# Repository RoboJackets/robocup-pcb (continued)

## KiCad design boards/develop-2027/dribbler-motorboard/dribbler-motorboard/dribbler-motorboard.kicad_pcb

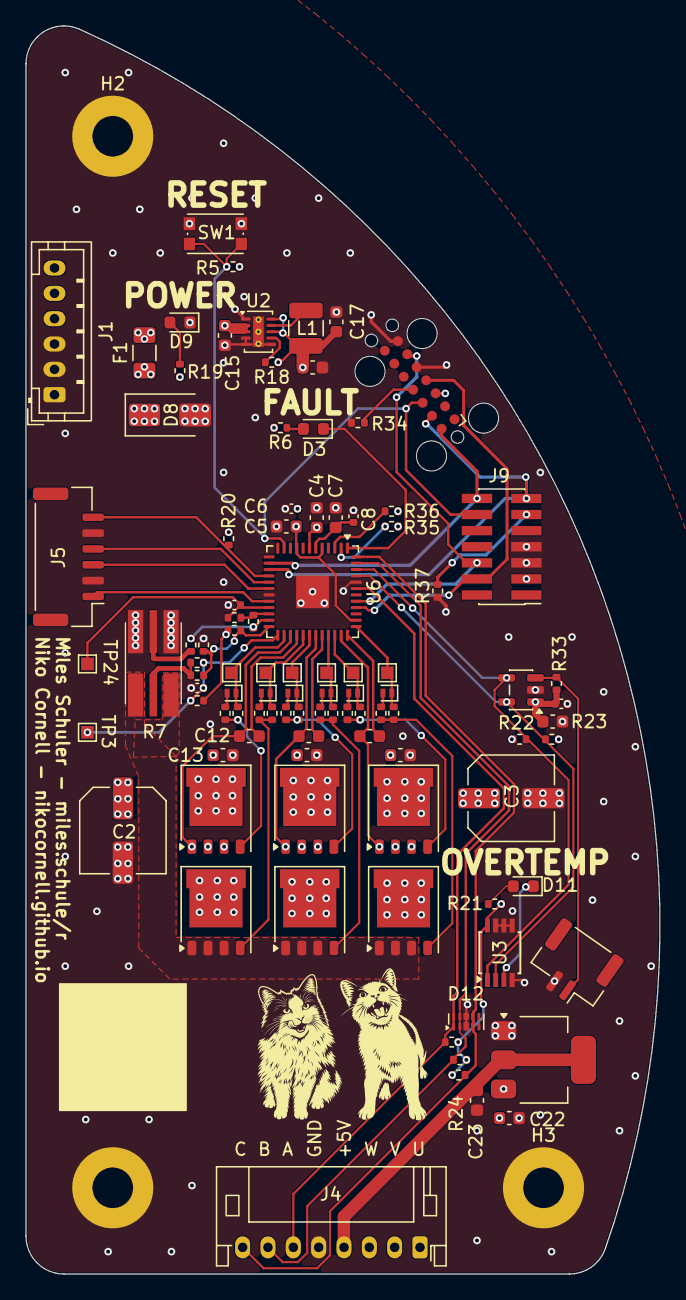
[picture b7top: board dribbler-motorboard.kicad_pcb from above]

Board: 4 copper layers, 50.0 x 98.5 mm, 101 parts (0 on the bottom side), 64 nets.

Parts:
C1, C4, C5, C9, C11, C12, C13, C14, C15, C23: 1u 63V; C_0603_1608Metric
C2, C3: 100u 35V; C_Elec_6.3x5.8
C6, C8, C20: 100n 25V; C_0402_1005Metric
C7, C16, C17, C19: 10u 25V; C_0603_1608Metric
C10: 33nF; C_0402_1005Metric
C18: 1n 25V; C_0402_1005Metric
C22: 4.7uF; C_0603_1608Metric
D1, D2, D4, D5, D6, D7: 1N4148WL2-TP; D_SOD-882
D3: FAULT; LED_0603_1608Metric
D8: SMAJ16A; D_SMA
D9: +12V; LED_0603_1608Metric
D11: OVERTEMP; LED_0603_1608Metric
D12: PUSB3FR4Z; Diodes_UDFN-10_1x2.5mm_P0.5mm
F1: 12A; Fuse_1206_3216Metric
H2, H3, H4: Corner; MountingHole_3.2mm_M3_Pad
J1: PWR_IN; JST_PH_B6B-PH-K_1x06_P2.00mm_Vertical
J4: MOTOR PHASE; JST_PH_S8B-PH-K_1x08_P2.00mm_Horizontal
J5: COMM SPI; JST_GH_BM06B-GHS-TBT_1x06-1MP_P1.25mm_Vertical
J7: Conn_01x02; JST_GH_SM02B-GHS-TB_1x02-1MP_P1.25mm_Horizontal
J8: Conn_ST_STDC14; Tag-Connect_TC2070-IDC-FP_2x07_P1.27mm_Vertical
J9: Conn_ST_STDC14; PinHeader_2x07_P1.27mm_Vertical_SMD
L1: 10u 540mA; L_1210_3225Metric
Q1, Q2, Q3, Q4, Q5, Q6: STL90N10F7; PQFN-8-EP_6x5mm_P1.27mm_Generic
R1, R3, R10, R12, R14, R16: 0R; R_0402_1005Metric
R2, R4, R11, R13, R15, R17: 68R; R_0402_1005Metric
R5, R19, R20, R24, R25, R26, R33, R35, R36: 10k; R_0402_1005Metric
R6, R21, R22, R23: 4.7k; R_0402_1005Metric
R7: 15m ±1% 3W; R_Shunt_Analog_2512_6332_HighAccuracy
R8: 1.13k ±0.1%; R_0402_1005Metric
R9: 33 ±0.1%; R_0402_1005Metric
R18: 100k; R_0402_1005Metric
R27: 120k ±0.1%; R_0402_1005Metric
R28, R31: 30k ±0.1%; R_0402_1005Metric
R29, R32: 240k ±0.1%; R_0402_1005Metric
R30: 300R ±1%; R_0402_1005Metric
R34, R37: 100; R_0402_1005Metric
SW1: RESET; SW_Push_1P1T_NO_CK_KMR2
TP3: OCCOMP; TestPoint_Pad_1.0x1.0mm
TP4: HSU; TestPoint_Pad_1.0x1.0mm
TP5: LSU; TestPoint_Pad_1.0x1.0mm
TP6: HSV; TestPoint_Pad_1.0x1.0mm
TP7: LSV; TestPoint_Pad_1.0x1.0mm
TP8: HSW; TestPoint_Pad_1.0x1.0mm
TP9: LSW; TestPoint_Pad_1.0x1.0mm
TP24: ISENSEx; TestPoint_Pad_1.0x1.0mm
U1: MCP3021; SOT-23-5
U2: TPS62177DQC; WSON-10-1EP_2x3mm_P0.5mm_EP0.84x2.4mm_ThermalVias
U3: LM75ADP; TSSOP-8_3x3mm_P0.65mm
U5: LDL1117S50R; SOT-223
U6: STSPIN32G0B2; VQFN-48-1EP_7x7mm_P0.5mm_EP2.6x2.6mm

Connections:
+3.3V: C5.1, C6.1, C16.1, C17.1, C19.1, C20.1, J8.3 (VCC), J9.3 (VCC), L1.2, R5.1, R6.1, R8.2, R18.1, R20.1, R21.1, R22.1, R23.1, R24.1, R25.1, R26.1, R29.1, R33.1, R35.1, R36.1, U1.1 (V_{DD}), U2.8 (~SLEEP), U2.10 (VOS), U3.8 (VCC), U6.5 (VDD), U6.9 (REG3V3), U6.38 (~STBY)
+5V: C22.1, J4.4 (+5V), U5.2 (VOUT), U5.4 (VOUT)
/External Connections/SPI.CSN: J5.6, R20.2, U6.16 (PA4/SPI1_~SS)
/External Connections/SPI.MISO: J5.3, U6.18 (PA6/SPI1_MISO)
/External Connections/SPI.MOSI: J5.1, U6.20 (PA7/SPI1_MOSI)
/External Connections/SPI.SCK: J5.4, U6.17 (PA5/SPI1_SCK)
/External Connections/SWD.CLK: J8.6 (JCLK/SWCLK), J9.6 (JCLK/SWCLK), U6.41 (PA14/SWCLK/BOOT0)
/External Connections/SWD.IO: J8.4 (JTMS/SWDIO), J9.4 (JTMS/SWDIO), U6.40 (PA13/SWDIO)
/External Connections/USART.RX: J8.13 (VCP_RX), J9.13 (VCP_RX), U6.15 (PA3/SPI2_MISO)
/External Connections/USART.TX: J8.14 (VCP_TX), J9.14 (VCP_TX), U6.14 (PA2/TIM2_CH3)
/External Connections/~RST: J8.12 (~RST), J9.12 (~RST), R5.2, SW1.2 (B), U6.11 (PF2/~RST)
/MOSFET Temperature Sensor/I2C.SCL: R23.2, U1.5 (SCL), U3.2 (SCL), U6.45 (PB6/I2C1_SCL)
/MOSFET Temperature Sensor/I2C.SDA: R22.2, U1.4 (SDA), U3.1 (SDA), U6.46 (PB7/I2C1_SDA)
/Motor Connections/HALL.A: D12.1 (CH1), D12.10 (CH1), J4.6 (HALL_A), R24.2, U6.43 (PB5)
/Motor Connections/HALL.B: D12.2 (CH2), D12.9 (CH2), J4.7 (HALL_B), R25.2, U6.47 (PB8)
/Motor Connections/HALL.C: D12.4 (CH3), D12.7 (CH3), J4.8 (HALL_C), R26.2, U6.48 (PB9)
/Motor Connections/MOTORU: C9.2, J4.1 (PHASE_U), Q1.1 (S), Q1.2 (S), Q1.3 (S), Q2.5 (D), U6.35 (OUTU)
/Motor Connections/MOTORV: C11.2, J4.2 (PHASE_V), Q3.1 (S), Q3.2 (S), Q3.3 (S), Q4.5 (D), U6.31 (OUTV)
/Motor Connections/MOTORW: C12.2, J4.3 (PHASE_W), Q5.1 (S), Q5.2 (S), Q5.3 (S), Q6.5 (D), U6.27 (OUTW)
/Motor Controller/Current Sensing/OPxN: R27.1, R28.2, U6.23 (OP1N)
/Motor Controller/Current Sensing/OPxO: R27.2, R30.1, U6.22 (OP1O)
/Motor Controller/Current Sensing/OPxP: R29.2, R31.2, R32.1, U6.24 (OP1P)
/Motor Controller/FAULT: D3.1 (K), U6.1 (PC13)
/Motor Controller/I_{SENSE}: C18.1, R30.2, TP24.1 (1_1), U6.21 (PB1/ADC_IN)
/Motor Controller/Motor Phase U/HSx: D1.1 (K), R2.1, TP4.1 (1_1), U6.34 (HSU)
/Motor Controller/Motor Phase U/LSx: D2.1 (K), R4.1, TP5.1 (1_1), U6.37 (LSU)
/Motor Controller/Motor Phase V/HSx: D4.1 (K), R11.1, TP6.1 (1_1), U6.30 (HSV)
/Motor Controller/Motor Phase V/LSx: D5.1 (K), R13.1, TP7.1 (1_1), U6.33 (LSV)
/Motor Controller/Motor Phase W/HSx: D6.1 (K), R15.1, TP8.1 (1_1), U6.26 (HSW)
/Motor Controller/Motor Phase W/LSx: D7.1 (K), R17.1, TP9.1 (1_1), U6.29 (LSW)
/Motor Controller/SHUNTN: R7.3, R28.1
/Motor Controller/SHUNTP: R7.2, R9.1, R31.1
/Motor Controller/SHUNT_H: Q2.1 (S), Q2.2 (S), Q2.3 (S), Q4.1 (S), Q4.2 (S), Q4.3 (S), Q6.1 (S), Q6.2 (S), Q6.3 (S), R7.1
/Motor Temperature Sensor/T_SENSE: J7.1, R33.2, U1.3 (A_{IN})
GND: C1.2, C2.2, C3.2, C4.2, C5.2, C6.2, C7.2, C8.2, C10.2, C13.2, C14.2, C15.2, C16.2, C17.2, C18.2, C19.2, C20.2, C22.2, C23.2, D8.2 (A2), D9.1 (K), D12.3 (GND), D12.8 (GND), H2.1 (1_1), H3.1 (1_1), H4.1 (1_1), J1.1, J1.2, J1.3, J4.5 (GND), J5.2, J5.5, J7.2, J8.5 (GND), J8.7 (GND), J9.5 (GND), J9.7 (GND), R7.4, R32.2, R34.1, R37.1, SW1.1 (A), U1.2 (V_{SS}), U2.1 (PGND), U2.4 (NC), U2.5 (FB), U2.6 (AGND), U2.11 (PAD), U3.4 (GND), U3.5 (A2), U3.6 (A1), U3.7 (A0), U5.1 (GND), U6.19 (TESTMODE), U6.44 (GND), U6.49 (EPAD)
unnamed: D1.2 (A), R1.1
unnamed: D2.2 (A), R3.1
unnamed: D3.2 (A), R6.2
unnamed: D4.2 (A), R10.1
unnamed: D5.2 (A), R12.1
unnamed: D6.2 (A), R14.1
unnamed: D7.2 (A), R16.1
unnamed: D9.2 (A), R19.2
unnamed: D11.2 (A), R21.2
unnamed: D11.1 (K), U3.3 (OS)
unnamed: F1.1, J1.4, J1.5, J1.6
unnamed: J8.11 (GNDDetect), R34.2
unnamed: J9.11 (GNDDetect), R37.2
unnamed: Q1.4 (G), R1.2, R2.2
unnamed: Q2.4 (G), R3.2, R4.2
unnamed: Q3.4 (G), R10.2, R11.2
unnamed: Q4.4 (G), R12.2, R13.2
unnamed: Q5.4 (G), R14.2, R15.2
unnamed: Q6.4 (G), R16.2, R17.2
unnamed: R18.2, U2.7 (PG)
unnamed: L1.1, U2.9 (SW)
unnamed: C7.1, C8.1, U6.6 (REG12)
unnamed: R35.2, U6.2 (PC14/OSC32_IN)
unnamed: R36.2, U6.3 (PC15/OSC32_OUT)
unnamed: C9.1, U6.36 (VBOOTU)
unnamed: C11.1, U6.32 (VBOOTV)
unnamed: C12.1, U6.28 (VBOOTW)
unnamed: C10.1, R8.1, R9.2, TP3.1 (1_1), U6.25 (OCCOMP)
VBUS: C1.1, C2.1, C3.1, C4.1, C13.1, C14.1, C15.1, C23.1, D8.1 (A1), F1.2, Q1.5 (D), Q3.5 (D), Q5.5 (D), R19.1, U2.2 (VIN), U2.3 (EN), U5.3 (VIN), U6.7 (VM)

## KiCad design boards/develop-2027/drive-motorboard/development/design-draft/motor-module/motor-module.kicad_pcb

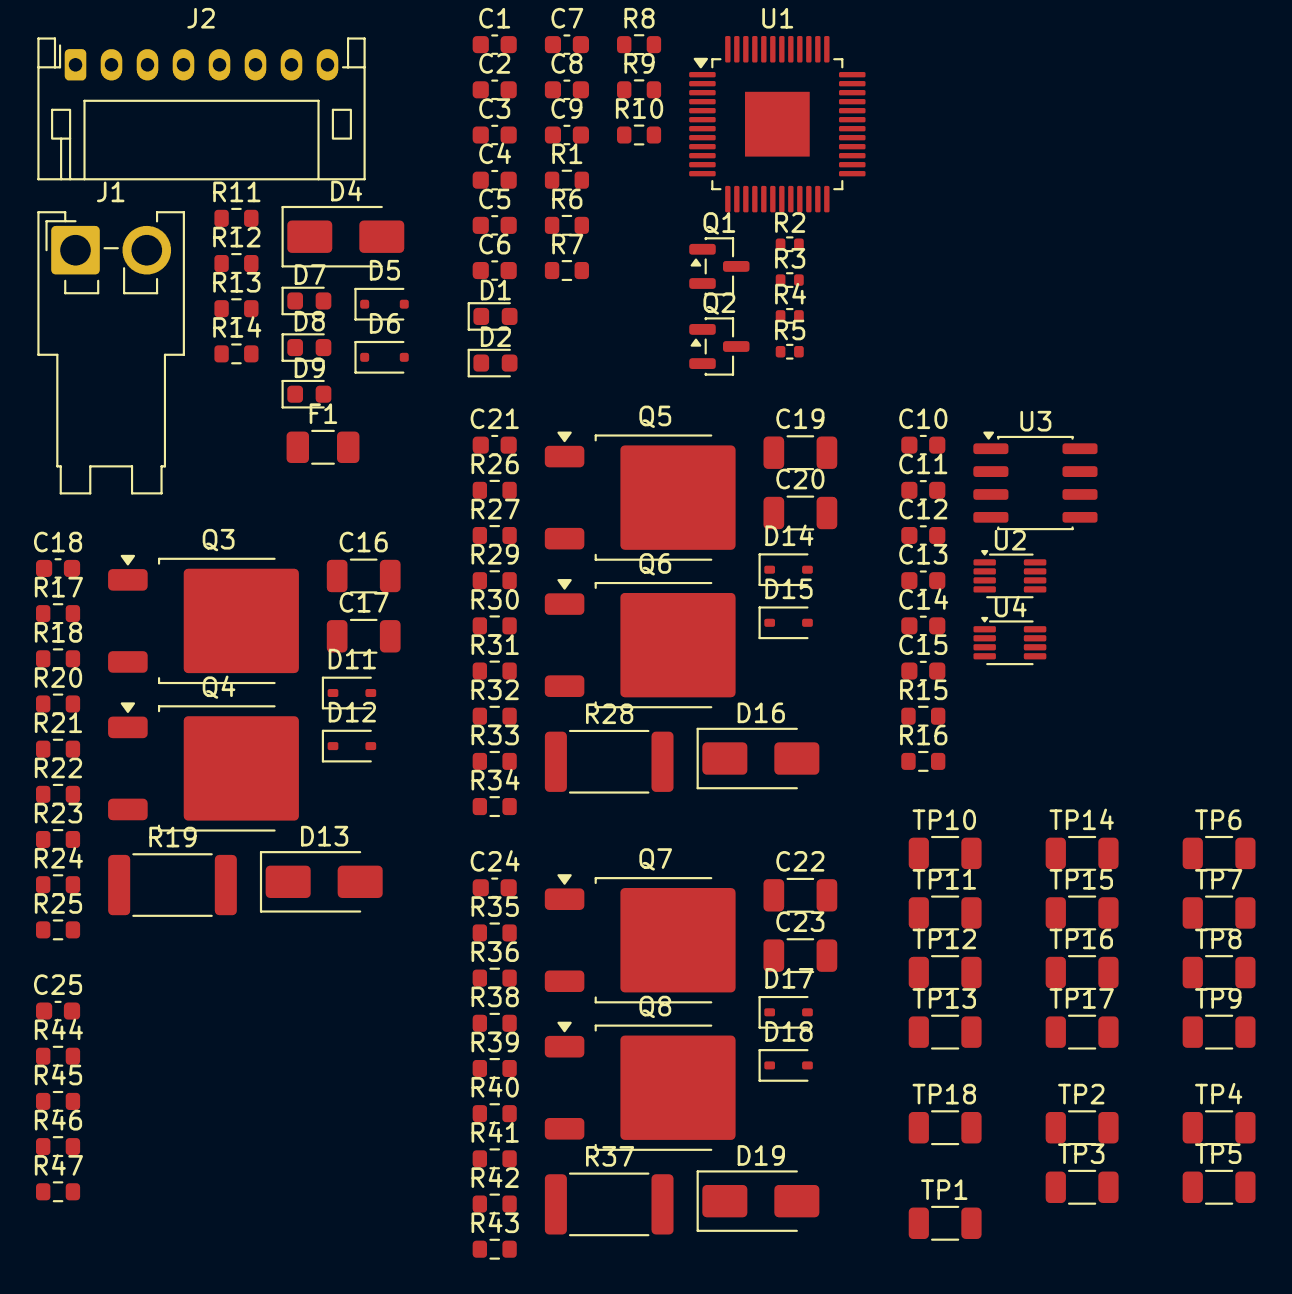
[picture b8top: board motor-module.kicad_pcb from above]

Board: 2 copper layers, 122 parts (0 on the bottom side), 74 nets, no tracks yet.

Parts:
C1, C4, C12, C13, C15: 100n; C_0603_1608Metric
C2, C5, C6, C7, C8, C9: 10u; C_0603_1608Metric
C3, C14: 1u; C_0603_1608Metric
C10, C11: 0.1n; C_0603_1608Metric
C16, C17, C19, C20, C22, C23: 10u; C_1206_3216Metric
C18, C21, C24, C25: 1n; C_0603_1608Metric
D1: FAULT; LED_0603_1608Metric
D2: DEBUG; LED_0603_1608Metric
D4, D13, D16, D19: SMAJ24CA; D_SMA
D5, D6: CUZ5V6,H3F; D_SOD-323F
D7: VDC OK; LED_0603_1608Metric
D8: 5V OK; LED_0603_1608Metric
D9: 3.3V OK; LED_0603_1608Metric
D11, D12, D14, D15, D17, D18: 1N4148WS; D_SOD-323
F1: 12 A 50 V; Fuse_1206_3216Metric
J1: Motor Power In; JST_VH_S2P-VH_1x02_P3.96mm_Horizontal
J2: Logical Conn.; JST_PH_S8B-PH-K_1x08_P2.00mm_Horizontal
Q1, Q2: BSS84AKW,115; SOT-23
Q3, Q4, Q5, Q6, Q7, Q8: STD140N6F7; TO-252-2
R1, R6, R7, R8: 10k; R_0603_1608Metric
R2, R3, R4, R5: 100; R_0402_1005Metric
R9, R10, R11, R12, R13, R14: 1k; R_0603_1608Metric
R15, R16, R17, R18, R25, R26, R27, R34, R35, R36, R43: 100; R_0603_1608Metric
R19, R28, R37: 5m±1% 3W; R_2512_6332Metric
R20, R23, R29, R32, R38, R41: 110±0.1%; R_0603_1608Metric
R21, R22, R30, R31, R39, R40: 6.04k±0.1%; R_0603_1608Metric
R24, R33, R42: 3.01k±0.1%; R_0603_1608Metric
R44, R45, R46: 3.3k; R_0603_1608Metric
R47: 15k; R_0603_1608Metric
TP1: RESET; R_1206_3216Metric
TP2: 5V; R_1206_3216Metric
TP3: 3.3V; R_1206_3216Metric
TP4: ENC_A; R_1206_3216Metric
TP5: ENC_B; R_1206_3216Metric
TP6, TP10, TP14: HS_x; R_1206_3216Metric
TP7, TP11, TP15: LS_x; R_1206_3216Metric
TP8, TP12, TP16: PHASE_x; R_1206_3216Metric
TP9, TP13, TP17: ISENSE_x; R_1206_3216Metric
TP18: OCCOMP; R_1206_3216Metric
U1: STSPIN32G0A2; LQFP-48-1EP_7x7mm_P0.5mm_EP3.6x3.6mm
U2, U4: SN74LVC3G17DCUR; VSSOP-8_2.3x2mm_P0.5mm
U3: SN75157DR; SOIC-8_3.9x4.9mm_P1.27mm

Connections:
+3.3V: C2.2, C3.2, C4.2, C12.1, C15.1, D6.1 (A1), J2.3, Q1.3 (D), Q2.3 (D), R1.1, R7.2, R8.2, R14.1, R21.2, R30.2, R39.2, R47.2, TP3.1, U1.5 (V_{DD}), U2.8 (Vcc), U4.8 (Vcc)
+5V: C13.1, C14.1, D5.1 (A1), J2.1, R13.1, TP2.1, U3.8 (Vcc)
/ENC_A: TP4.1, U1.43 (PB6), U4.7 (1Y)
/ENC_B: TP5.1, U1.45 (PB7), U4.5 (2Y)
/H1: U1.15 (PA3), U2.7 (1Y)
/H2: U1.16 (PA4), U2.5 (2Y)
/H3: U1.17 (PA5), U2.2 (3Y)
/Microcontroller/DEBUG: Q2.1 (G), R7.1, U1.10 (PF0)
/Microcontroller/FAULT: Q1.1 (G), R6.1, U1.1 (PC14)
/Microcontroller/HS_U: D11.1 (K), R17.1, TP6.1, U1.34 (HSU)
/Microcontroller/HS_V: D14.1 (K), R26.1, TP10.1, U1.30 (HSV)
/Microcontroller/HS_W: D17.1 (K), R35.1, TP14.1, U1.26 (HSW)
/Microcontroller/ISENSE_U: R24.2, R25.2, TP9.1, U1.12 (PA0), U1.22 (OP1O)
/Microcontroller/ISENSE_V: R33.2, R34.2, TP13.1, U1.4 (OP2O), U1.20 (PA7)
/Microcontroller/ISENSE_W: R42.2, R43.2, TP17.1, U1.21 (PB1), U1.48 (OP3O)
/Microcontroller/LS_U: D12.1 (K), R18.1, TP7.1, U1.37 (LSU)
/Microcontroller/LS_V: D15.1 (K), R27.1, TP11.1, U1.33 (LSV)
/Microcontroller/LS_W: D18.1 (K), R36.1, TP15.1, U1.29 (LSW)
/Microcontroller/OP_U_N: R23.2, R24.1, U1.23 (OP1N)
/Microcontroller/OP_U_P: R20.2, R21.1, R22.2, U1.24 (OP1P)
/Microcontroller/OP_V_N: R32.2, R33.1, U1.3 (OP2N)
/Microcontroller/OP_V_P: R29.2, R30.1, R31.2, U1.2 (OP2P)
/Microcontroller/OP_W_N: R41.2, R42.1, U1.47 (OP3N)
/Microcontroller/OP_W_P: R38.2, R39.1, R40.2, U1.46 (OP3P)
/Microcontroller/SPI1_CE_USART2_RX: J2.8, R5.1
/Microcontroller/SPI1_MISO: J2.7, R4.1
/Microcontroller/SPI1_MOSI_USART2_TX: J2.6, R3.1
/Microcontroller/SPI1_SCK: J2.5, R2.1
/Microcontroller/~RESET: R8.1, TP1.1, U1.11 (~RST)
/Motor Interface/EN_CH_A: R15.1, U3.1 (1IN+)
/Motor Interface/EN_CH_B: R16.1, U3.6 (2IN+)
/Motor Interface/~EN_CH_A: C10.2, U3.7 (1IN-)
/Motor Interface/~EN_CH_B: C11.2, U3.5 (2IN-)
/OCCOMP: C25.1, R44.2, R45.2, R46.2, R47.1, TP18.1, U1.25 (OCCOMP)
/PHASE_U: C7.1, D13.2 (A2), Q3.3, Q4.1, TP8.1, U1.35 (OUTU)
/PHASE_V: C8.1, D16.2 (A2), Q5.3, Q6.1, TP12.1, U1.31 (OUTV)
/PHASE_W: C9.1, D19.2 (A2), Q7.3, Q8.1, TP16.1, U1.27 (OUTW)
/SHUNT_U: Q4.3, R19.1, R20.1, R44.1
/SHUNT_V: Q6.3, R28.1, R29.1, R45.1
/SHUNT_W: Q8.3, R37.1, R38.1, R46.1
GND: C1.2, C2.1, C3.1, C4.1, C5.1, C6.2, C12.2, C13.2, C14.2, C15.2, C16.2, C17.2, C18.1, C19.2, C20.2, C21.1, C22.2, C23.2, C24.1, C25.2, D1.1 (K), D2.1 (K), D4.1 (A1), D5.2 (A2), D6.2 (A2), D7.1 (K), D8.1 (K), D9.1 (K), D13.1 (A1), D16.1 (A1), D19.1 (A1), J1.2, J2.2, J2.4, R6.2, R19.2, R22.1, R23.1, R28.2, R31.1, R32.1, R37.2, R40.1, R41.1, U1.19 (TESTMODE), U1.44 (GND), U1.49 (GND_PAD), U2.4 (GND), U3.4 (GND), U4.4 (GND)
unnamed: C10.1, R15.2
unnamed: C11.1, R16.2
unnamed: C18.2, R25.1
unnamed: C21.2, R34.1
unnamed: C24.2, R43.1
unnamed: D1.2 (A), R9.2
unnamed: D2.2 (A), R10.2
unnamed: D7.2 (A), R12.2
unnamed: D8.2 (A), R13.2
unnamed: D9.2 (A), R14.2
unnamed: D11.2 (A), Q3.2, R17.2
unnamed: D12.2 (A), Q4.2, R18.2
unnamed: D14.2 (A), Q5.2, R26.2
unnamed: D15.2 (A), Q6.2, R27.2
unnamed: D17.2 (A), Q7.2, R35.2
unnamed: D18.2 (A), Q8.2, R36.2
unnamed: F1.1, J1.1
unnamed: Q1.2 (S), R9.1
unnamed: Q2.2 (S), R10.1
unnamed: R11.2, R12.1
unnamed: R2.2, U1.13 (PA1)
unnamed: R3.2, U1.14 (PA2)
unnamed: R4.2, U1.18 (PA6)
unnamed: R5.2, U1.42 (PA15)
unnamed: C6.1, U1.9 (REG_3V3)
unnamed: C5.2, U1.6 (REG_12V)
unnamed: C7.2, U1.36 (VBOOTU)
unnamed: C8.2, U1.32 (VBOOTV)
unnamed: C9.2, U1.28 (VBOOTW)
unnamed: C1.1, R1.2, U1.38 (~STBY)
unnamed: U3.2 (1OUT), U4.1 (1A)
unnamed: U3.3 (2OUT), U4.3 (2A)
VDC: C16.1, C17.1, C19.1, C20.1, C22.1, C23.1, D4.2 (A2), F1.2, Q3.1, Q5.1, Q7.1, R11.1, U1.7 (VM)

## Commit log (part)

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2026-04-10 ordered version 4-10-26
2026-04-30 remove unused submodules
2026-04-30 move inactive board to archive
2026-04-30 promote kicker-3.4 to mainline
2026-04-30 move modular motorboard to new scheme
2026-04-30 reorganize existing content to draft folder
2026-05-01 add skeleton
2026-05-01 Add schematic
2026-05-01 add AS5047 breakout board
2026-05-02 v1.1 - leave unused U/V floating instead of drive low
2026-05-02 add manufacturing notes for 1.1
2026-05-03 fix pcb formatting
2026-05-03 as5047p breakout test results
2026-05-03 Add application notes for AS5047P
2026-05-03 update magnet recommendation
2026-05-03 move obsidian vault for naming purposes
2026-05-05 notes from STSPIN32G0A2 datasheet
2026-05-05 Add application notes for power MOSFET
2026-05-05 Add notes from ST Application Notes
2026-05-05 Add reference materials for LM75A
2026-05-05 Application notes for LM75
2026-05-06 Add note about motor connectors
2026-05-07 Select shunt resistor
2026-05-07 select VBATT fuse
2026-05-08 Start on integration test board
2026-05-11 add results from more testing
2026-05-21 Add notes about motor connector part selection
2026-05-21 Add current sense, over-current circuits
2026-05-22 Add power stage
2026-05-22 Add test points
2026-05-24 Finish motor controller section
2026-05-25 Added power and connectors
2026-05-26 reformat root sheet, assign parts numbers for generics
2026-05-26 Set up PCB design rules
2026-06-30 remote sync
